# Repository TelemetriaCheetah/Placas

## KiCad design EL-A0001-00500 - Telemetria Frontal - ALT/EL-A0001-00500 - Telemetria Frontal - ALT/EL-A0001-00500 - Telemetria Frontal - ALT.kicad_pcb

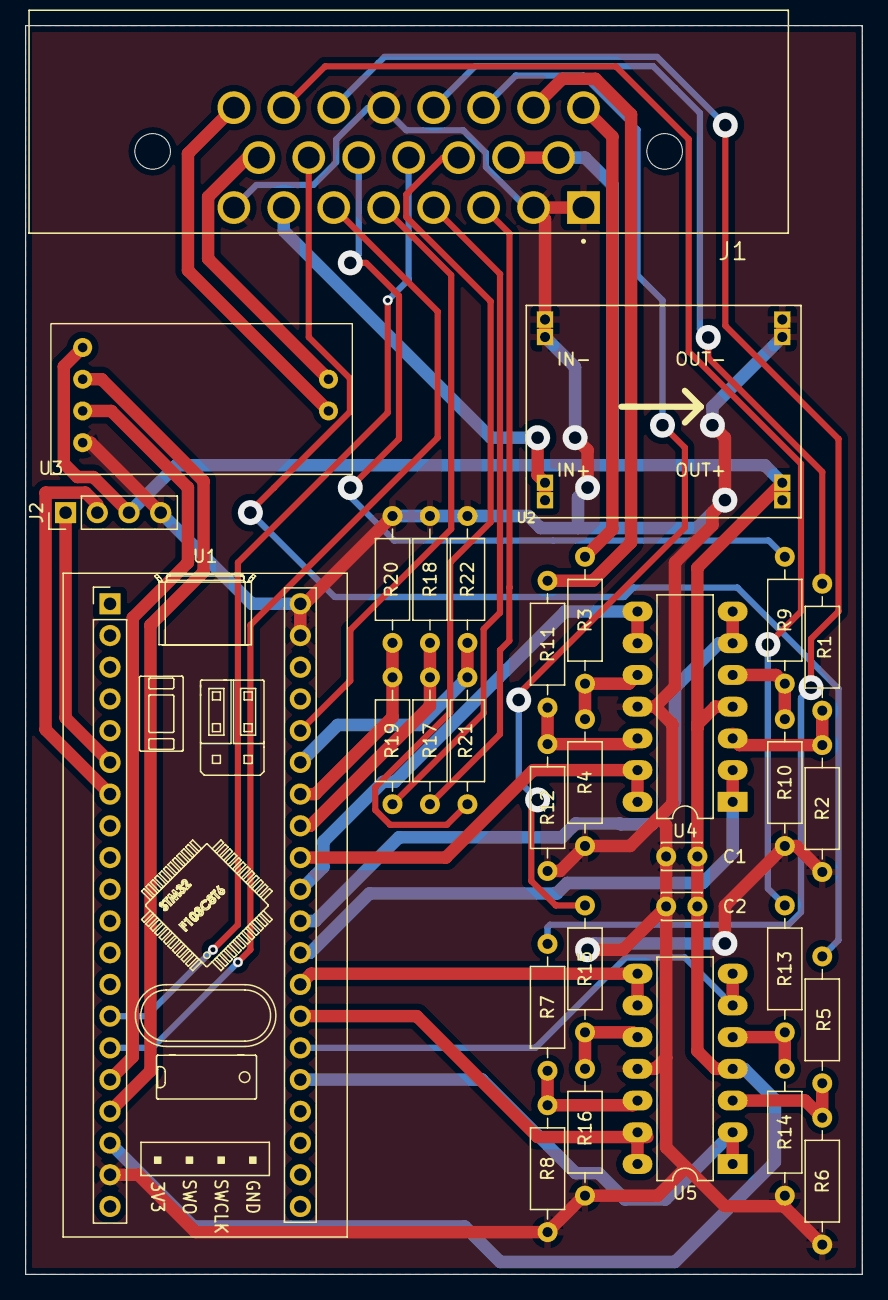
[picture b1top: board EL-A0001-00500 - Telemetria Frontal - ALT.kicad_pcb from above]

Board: 2 copper layers, 67.0 x 100.0 mm, 31 parts (0 on the bottom side), 42 nets.

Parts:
C1, C2: 100nF; C_Disc_D3.0mm_W2.0mm_P2.50mm
J1: 1-776087-1; TE_1-776087-1
J2: UART; PinHeader_1x04_P2.54mm_Vertical
R1, R2, R3, R4, R5, R6, R7, R8, R9, R10, R11, R12, R13, R14, R15, R16, R18, R20, R22: 10K; R_Axial_DIN0207_L6.3mm_D2.5mm_P10.16mm_Horizontal
R17, R19, R21: 30K; R_Axial_DIN0207_L6.3mm_D2.5mm_P10.16mm_Horizontal
U1: YAAJ_BluePill; YAAJ_BluePill_1
U2: MP1584; DC-BRICK
U3: TJA1050-Module
U4, U5: LM324; DIP-14_W7.62mm_LongPads

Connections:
+5V: C1.1, C2.1, J1.9, J1.10, J2.3, U1.18 (5V), U2.7 (VOUT+), U2.8 (VOUT+), U3.1 (VCC), U4.4 (V+), U5.4 (V+)
+12V: J1.7, U2.3 (VIN+), U2.4 (VIN+)
ADC_IN_1: J1.14, R5.1
ADC_IN_2: J1.22, R13.1
ADC_IN_3: J1.21, R7.1
ADC_OUT_1: U1.25 (PA0), U5.1, U5.2 (-)
ADC_OUT_2: U1.26 (PA1), U5.6 (-), U5.7
ADC_OUT_3: U1.27 (PA2), U5.13 (-), U5.14
BOTS_IN: J1.3, R17.1
BOTS_OUT: R17.2, R18.1, U1.33 (PB0)
CAN_H: J1.15, U3.5 (CANH)
CAN_L: J1.23, U3.6 (CANL)
CAN_RX: U1.16 (PB8), U3.3 (RX)
CAN_TX: U1.17 (PB9), U3.2 (TX)
FREIOS_IN_1: J1.13, R9.1
FREIOS_IN_2: J1.16, R3.1
FREIOS_IN_3: J1.17, R11.1
FREIOS_OUT_1: U1.30 (PA5), U4.6 (-), U4.7
FREIOS_OUT_2: U1.31 (PA6), U4.8, U4.9 (-)
FREIOS_OUT_3: U1.32 (PA7), U4.13 (-), U4.14
GND: C1.2, C2.2, J1.1, J1.2, J1.8, J1.20, J2.4, R2.2, R4.2, R6.2, R8.2, R10.2, R12.2, R14.2, R16.2, R18.2, R20.2, R22.2, U1.19 (GND), U1.39 (GND), U1.40 (GND), U2.1 (VIN-), U2.2 (VIN-), U2.5 (VOUT-), U2.6 (VOUT-), U3.4 (GND), U4.11 (V-), U5.11 (V-)
INERTIA_IN: J1.4, R19.1
INERTIA_OUT: R19.2, R20.1, U1.34 (PB1)
unnamed: J2.1, U1.6 (PA9)
unnamed: J2.2, U1.7 (PA10)
unnamed: R1.2, R2.1, U4.3 (+)
unnamed: R3.2, R4.1, U4.10 (+)
unnamed: R5.2, R6.1, U5.3 (+)
unnamed: R7.2, R8.1, U5.12 (+)
unnamed: R9.2, R10.1, U4.5 (+)
unnamed: R11.2, R12.1, U4.12 (+)
unnamed: R13.2, R14.1, U5.5 (+)
unnamed: R15.2, R16.1, U5.10 (+)
PWT_IN_1: J1.5, U1.36 (PB11)
PWT_IN_2: J1.6, U1.15 (PB7)
PWT_IN_4: J1.12, U1.14 (PB6)
SHUT_IN: J1.11, R21.1
SHUT_OUT: R21.2, R22.1, U1.35 (PB10)
TPS_IN_1: J1.18, R15.1
TPS_IN_2: J1.19, R1.1
TPS_OUT_1: U1.28 (PA3), U5.8, U5.9 (-)
TPS_OUT_2: U1.29 (PA4), U4.1, U4.2 (-)

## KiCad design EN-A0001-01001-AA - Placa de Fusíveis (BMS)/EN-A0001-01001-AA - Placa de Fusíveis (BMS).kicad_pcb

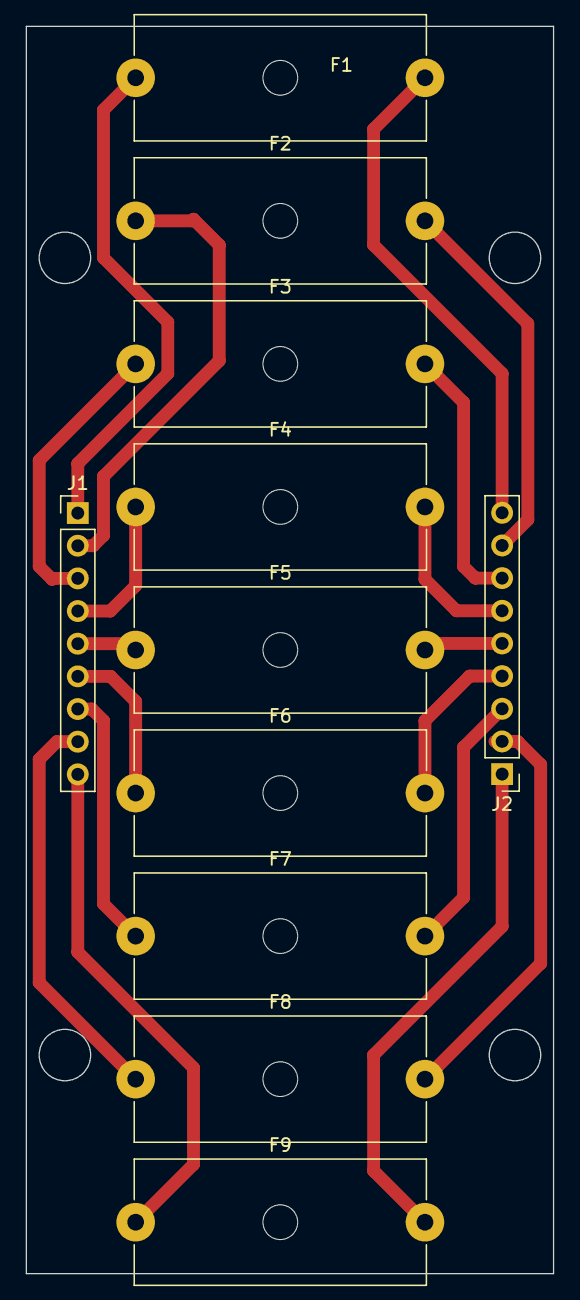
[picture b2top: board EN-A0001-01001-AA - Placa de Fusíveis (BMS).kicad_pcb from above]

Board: 2 copper layers, 41.0 x 97.0 mm, 11 parts (0 on the bottom side), 18 nets.

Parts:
F1, F2, F3, F4, F5, F6, F7, F8, F9: Fuse; Fuseholder_Cylinder-5x20mm_Schurter_0031_8201_Horizontal_Op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
J1, J2: Conn_01x09_Male; PinHeader_1x09_P2.54mm_Vertical

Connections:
unnamed: F1.1, J1.1
unnamed: F1.2, J2.9
unnamed: F2.1, J1.2
unnamed: F2.2, J2.8
unnamed: F3.1, J1.3
unnamed: F3.2, J2.7
unnamed: F4.1, J1.4
unnamed: F4.2, J2.6
unnamed: F5.1, J1.5
unnamed: F5.2, J2.5
unnamed: F6.1, J1.6
unnamed: F6.2, J2.4
unnamed: F7.1, J1.7
unnamed: F7.2, J2.3
unnamed: F8.1, J1.8
unnamed: F8.2, J2.2
unnamed: F9.1, J1.9
unnamed: F9.2, J2.1

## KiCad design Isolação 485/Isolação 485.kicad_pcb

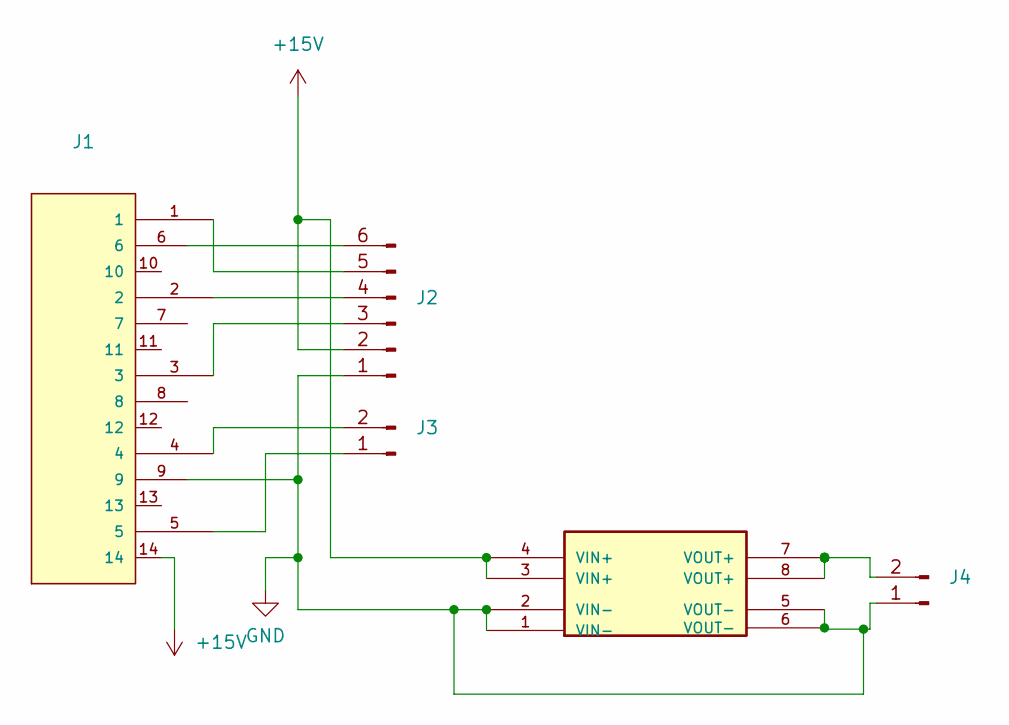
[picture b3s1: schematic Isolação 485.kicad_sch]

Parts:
J1: 776266-2
J2: Conn_01x06_Male
J3: Conn_01x02_Male
J4: (no value)
U1: MP1584

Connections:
+15V: J1.14, J2.2, U1.3 (VIN+), U1.4 (VIN+)
GND: J1.9, J2.1, J4.1, U1.1 (VIN-), U1.2 (VIN-), U1.5 (VOUT-), U1.6 (VOUT-)
unnamed: J1.2, J2.4
unnamed: J1.6, J2.6
unnamed: J1.3, J2.3
unnamed: J1.1, J2.5
unnamed: J1.5, J3.1
unnamed: J1.4, J3.2
unnamed: J4.2, U1.7 (VOUT+), U1.8 (VOUT+)

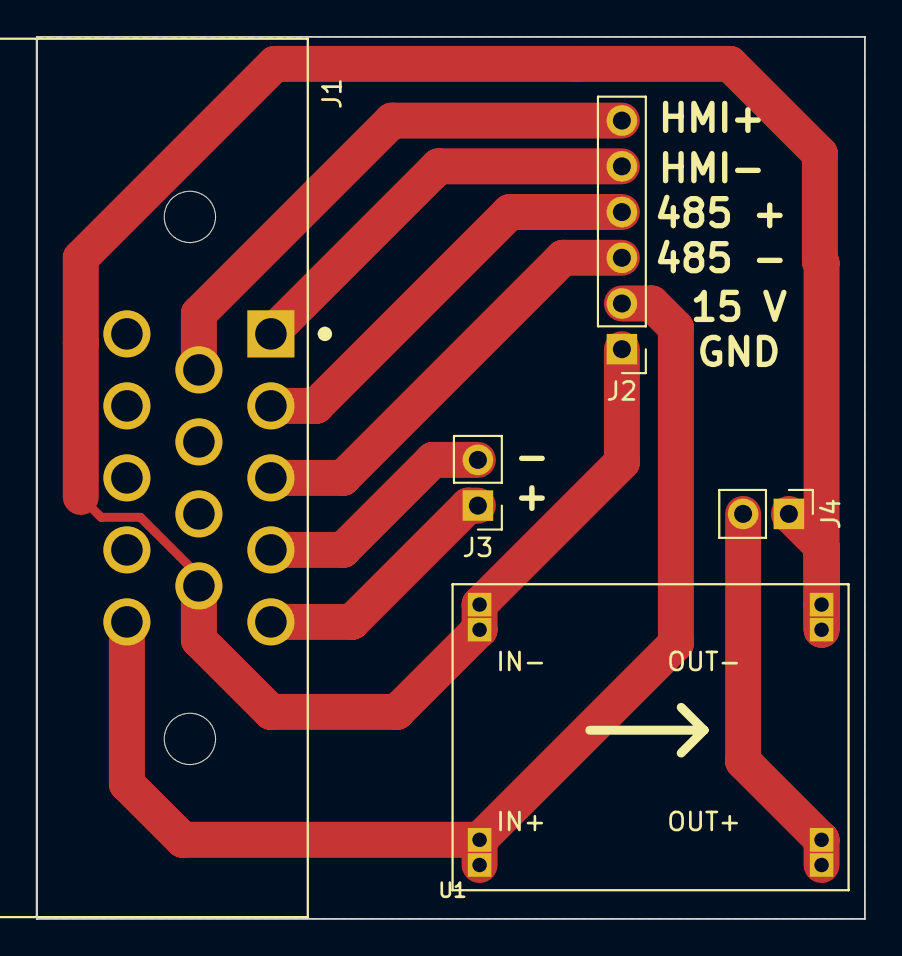
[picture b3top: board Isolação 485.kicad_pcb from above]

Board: 2 copper layers, 46.0 x 49.0 mm, 5 parts (0 on the bottom side), 9 nets.

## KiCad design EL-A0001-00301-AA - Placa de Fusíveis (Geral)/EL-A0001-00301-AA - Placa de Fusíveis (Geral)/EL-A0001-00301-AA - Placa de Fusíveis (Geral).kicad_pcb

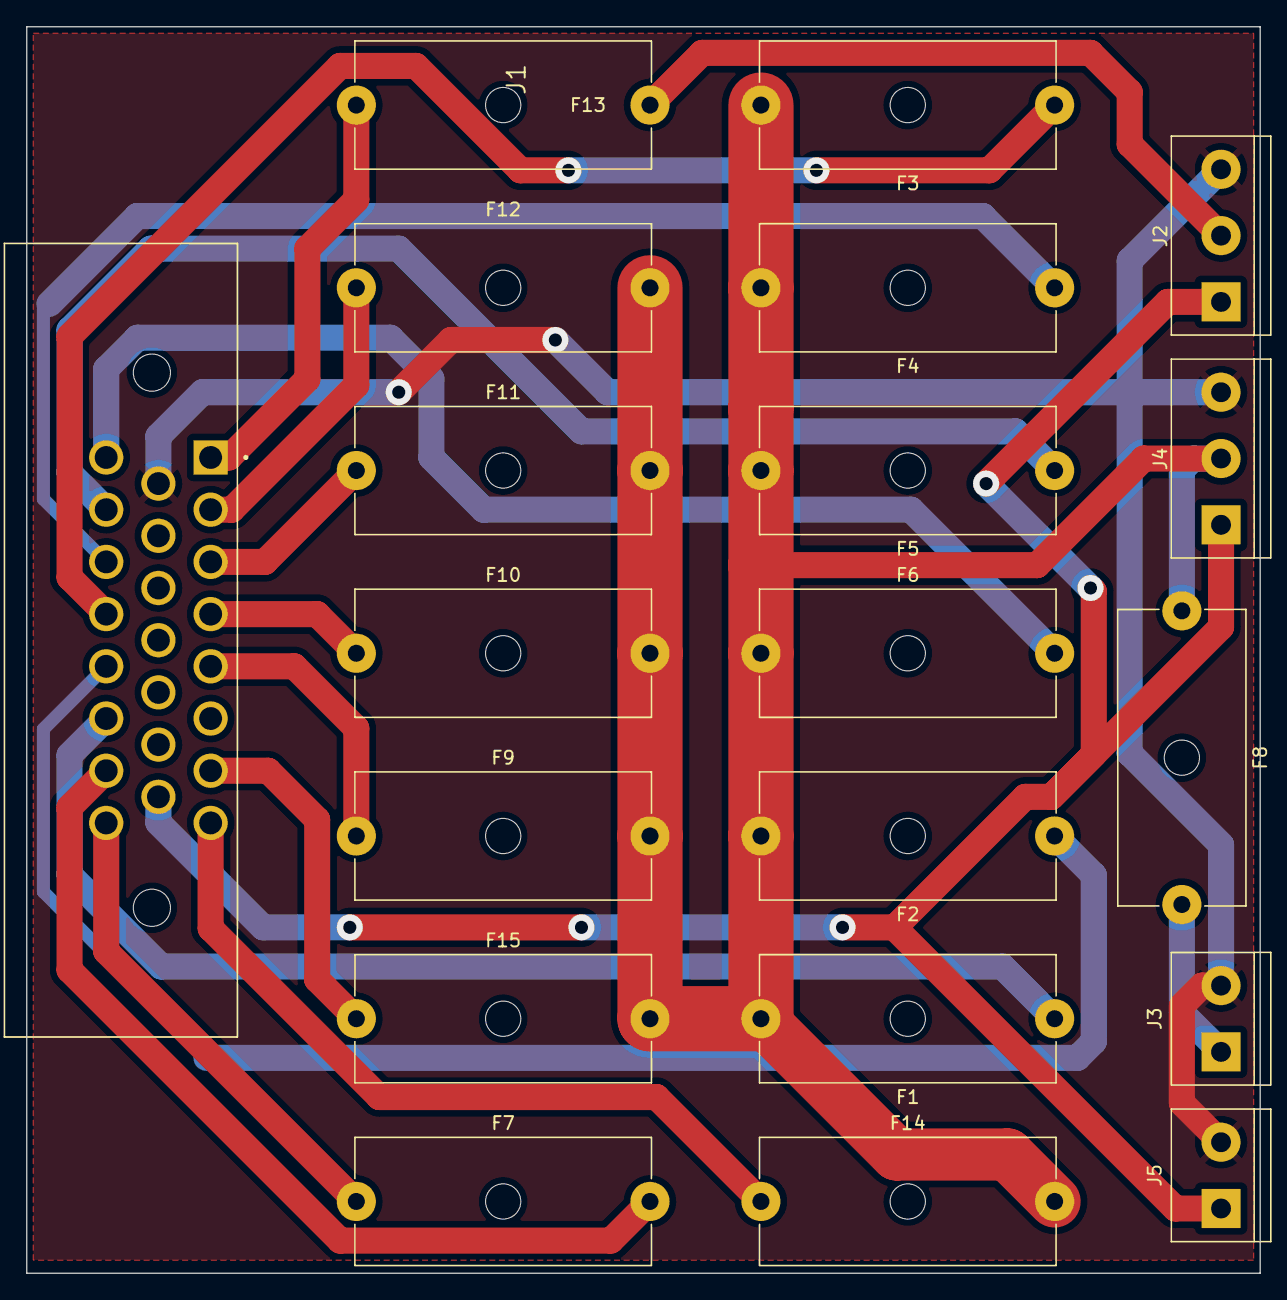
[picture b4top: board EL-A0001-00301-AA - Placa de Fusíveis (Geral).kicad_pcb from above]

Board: 2 copper layers, 94.5 x 95.5 mm, 20 parts (0 on the bottom side), 20 nets.

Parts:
F1, F2, F3, F4, F5, F6, F9, F10, F11, F12, F14, F15: Fuse; Fuseholder_Cylinder-5x20mm_Schurter_0031_8201_Horizontal_Op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
F7: GLV_FUSE; Fuseholder_Cylinder-5x20mm_Schurter_0031_8201_Horizontal_Op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
F8: SPLIT_FUSE; Fuseholder_Cylinder-5x20mm_Schurter_0031_8201_Horizontal_Op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
F13: SHUT_FUSE; Fuseholder_Cylinder-5x20mm_Schurter_0031_8201_Horizontal_Op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
J1: 1-776087-1; TE_1-776087-1
J2: BUCK_SHUT; TerminalBlock_bornier-3_P5.08mm
J3: SPLIT_POWER; TerminalBlock_bornier-2_P5.08mm
J4: DC_CONVERTER; TerminalBlock_bornier-3_P5.08mm
J5: VBAT; TerminalBlock_bornier-2_P5.08mm

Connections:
12V: F1.2, F2.2, F3.2, F4.2, F5.2, F6.2, F8.1, F9.2, F10.2, F11.2, F12.2, F14.2, F15.2, J4.2
GND: J1.9, J2.3, J3.2, J4.3, J5.2
unnamed: F1.1, J1.21
unnamed: F2.1, J1.20
unnamed: F3.1, J1.19
unnamed: F4.1, J1.18
unnamed: F5.1, J1.17
unnamed: F6.1, J1.16
unnamed: F7.1, J1.23
unnamed: F8.2, J3.1
unnamed: F9.1, J1.5
unnamed: F10.1, J1.4
unnamed: F11.1, J1.3
unnamed: F12.1, J1.2
unnamed: F14.1, J1.8
unnamed: F15.1, J1.7
unnamed: F13.1, J1.1
unnamed: F7.2, J1.22
unnamed: F13.2, J2.2
VBAT: J1.15, J2.1, J4.1, J5.1

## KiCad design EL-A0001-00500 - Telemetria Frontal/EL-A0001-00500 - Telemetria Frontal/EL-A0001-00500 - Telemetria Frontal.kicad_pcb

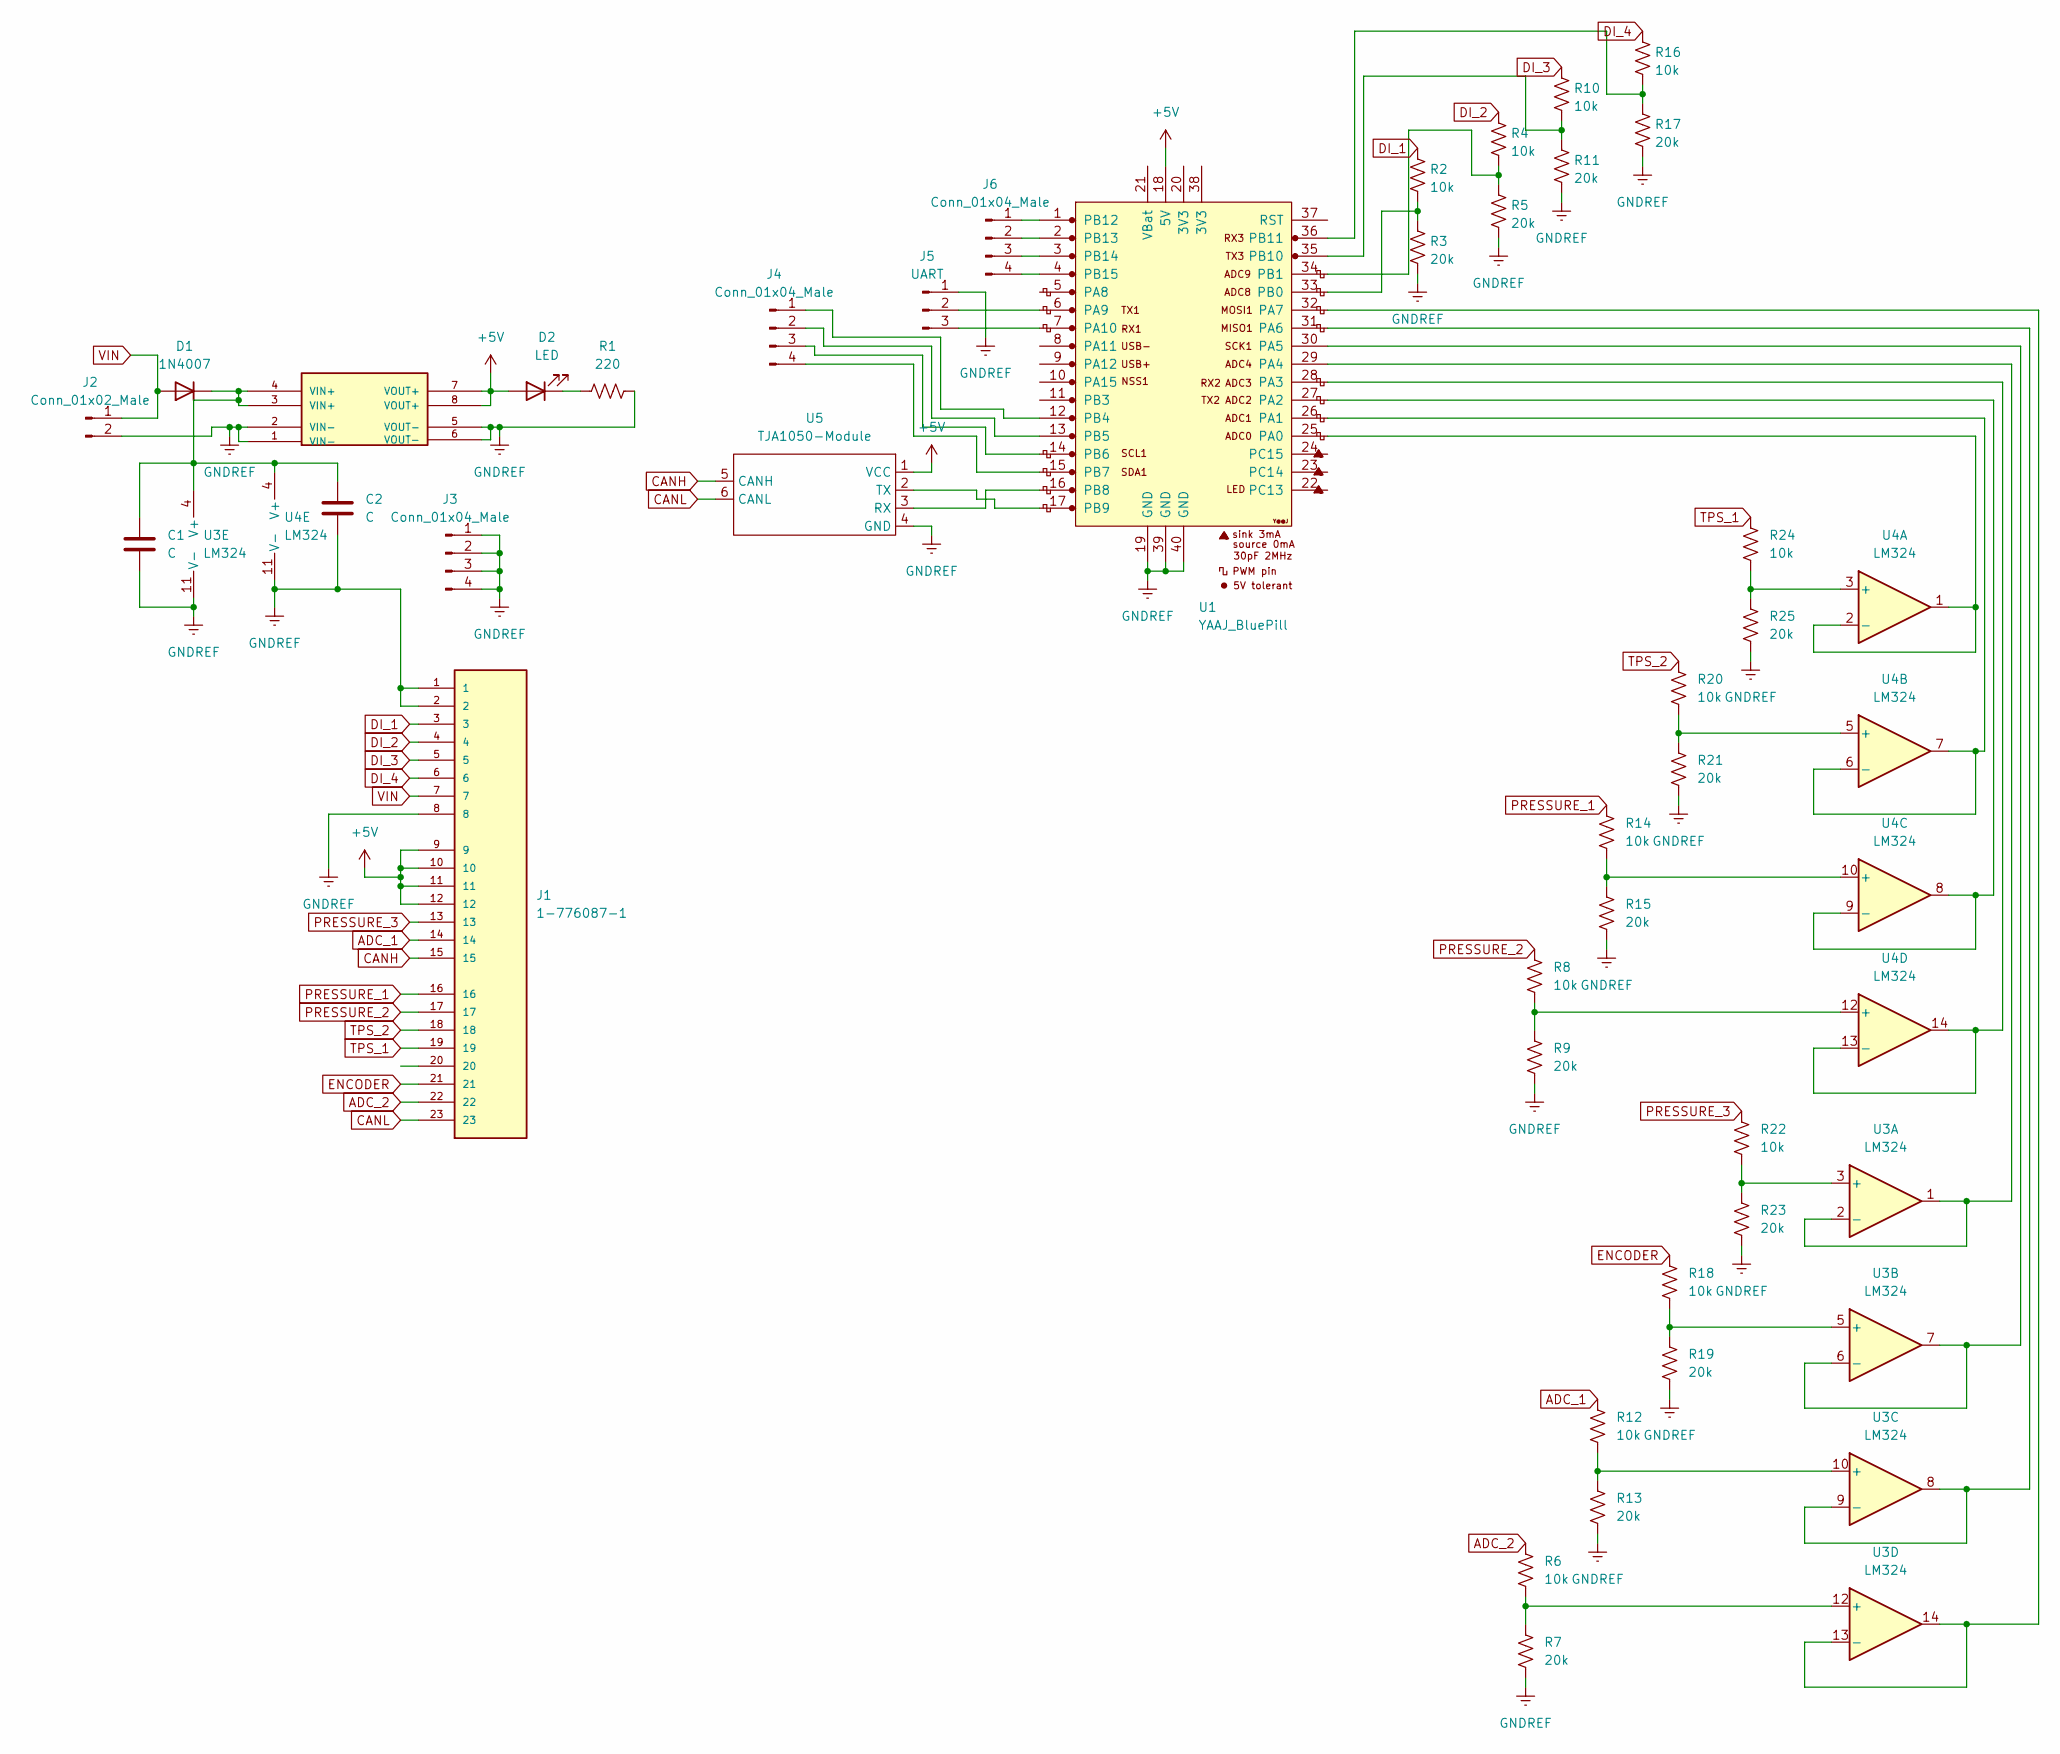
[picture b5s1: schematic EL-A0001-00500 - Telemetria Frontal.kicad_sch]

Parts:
C1, C2: C; C_0805_2012Metric
D1: 1N4007; D_DO-41_SOD81_P10.16mm_Horizontal
D2: LED; LED_D5.0mm
J1: 1-776087-1; TE_1-776087-1
J2: Conn_01x02_Male; PinHeader_1x02_P2.54mm_Vertical
J3, J4, J6: Conn_01x04_Male; PinHeader_1x04_P2.54mm_Vertical
J5: UART; PinHeader_1x03_P2.54mm_Vertical
R1: 220; R_0805_2012Metric
R2, R4, R10, R16: 10k; R_Axial_DIN0207_L6.3mm_D2.5mm_P10.16mm_Horizontal
R3, R5, R11, R17: 20k; R_Axial_DIN0207_L6.3mm_D2.5mm_P10.16mm_Horizontal
R6, R8, R12, R14, R18, R20, R22, R24: 10k; R_0805_2012Metric
R7, R9, R13, R15, R19, R21, R23, R25: 20k; R_0805_2012Metric
U1: YAAJ_BluePill; YAAJ_BluePill_1
U2: MP1584; DC-BRICK
U3, U4: LM324; DIP-14_W7.62mm_LongPads
U5: TJA1050-Module

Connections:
+5V: D2.2 (A), J1.9, J1.10, J1.11, J1.12, U1.18 (5V), U2.7 (VOUT+), U2.8 (VOUT+), U5.1 (VCC)
ADC_1: J1.14, R12.2
ADC_2: J1.22, R6.2
CANH: J1.15, U5.5 (CANH)
CANL: J1.23, U5.6 (CANL)
DI_1: J1.3, R2.2
DI_2: J1.4, R4.2
DI_3: J1.5, R10.2
DI_4: J1.6, R16.2
ENCODER: J1.21, R18.2
GNDREF: C1.2, C2.2, J1.1, J1.2, J1.8, J2.2, J3.1, J3.2, J3.3, J3.4, J5.1, R1.2, R3.1, R5.1, R7.1, R9.1, R11.1, R13.1, R15.1, R17.1, R19.1, R21.1, R23.1, R25.1, U1.19 (GND), U1.39 (GND), U1.40 (GND), U2.1 (VIN-), U2.2 (VIN-), U2.5 (VOUT-), U2.6 (VOUT-), U3.11 (V-), U4.11 (V-), U5.4 (GND)
unnamed: C1.1, C2.1, D1.1 (K), U2.3 (VIN+), U2.4 (VIN+), U3.4 (V+), U4.4 (V+)
unnamed: D2.1 (K), R1.1
unnamed: J4.1, U1.12 (PB4)
unnamed: J4.2, U1.13 (PB5)
unnamed: J4.3, U1.14 (PB6)
unnamed: J4.4, U1.15 (PB7)
unnamed: J5.2, U1.6 (PA9)
unnamed: J5.3, U1.7 (PA10)
unnamed: J6.1, U1.1 (PB12)
unnamed: J6.2, U1.2 (PB13)
unnamed: J6.3, U1.3 (PB14)
unnamed: J6.4, U1.4 (PB15)
unnamed: R2.1, R3.2, U1.33 (PB0)
unnamed: R4.1, R5.2, U1.34 (PB1)
unnamed: R6.1, R7.2, U3.12 (+)
unnamed: R8.1, R9.2, U4.12 (+)
unnamed: R10.1, R11.2, U1.35 (PB10)
unnamed: R12.1, R13.2, U3.10 (+)
unnamed: R14.1, R15.2, U4.10 (+)
unnamed: R16.1, R17.2, U1.36 (PB11)
unnamed: R18.1, R19.2, U3.5 (+)
unnamed: R20.1, R21.2, U4.5 (+)
unnamed: R22.1, R23.2, U3.3 (+)
unnamed: R24.1, R25.2, U4.3 (+)
unnamed: U1.16 (PB8), U5.3 (RX)
unnamed: U1.17 (PB9), U5.2 (TX)
unnamed: U1.25 (PA0), U4.1, U4.2 (-)
unnamed: U1.26 (PA1), U4.6 (-), U4.7
unnamed: U1.27 (PA2), U4.8, U4.9 (-)
unnamed: U1.28 (PA3), U4.13 (-), U4.14
unnamed: U1.29 (PA4), U3.1, U3.2 (-)
unnamed: U1.30 (PA5), U3.6 (-), U3.7
unnamed: U1.31 (PA6), U3.8, U3.9 (-)
unnamed: U1.32 (PA7), U3.13 (-), U3.14
PRESSURE_1: J1.16, R14.2
PRESSURE_2: J1.17, R8.2
PRESSURE_3: J1.13, R22.2
TPS_1: J1.19, R24.2
TPS_2: J1.18, R20.2
VIN: D1.2 (A), J1.7, J2.1

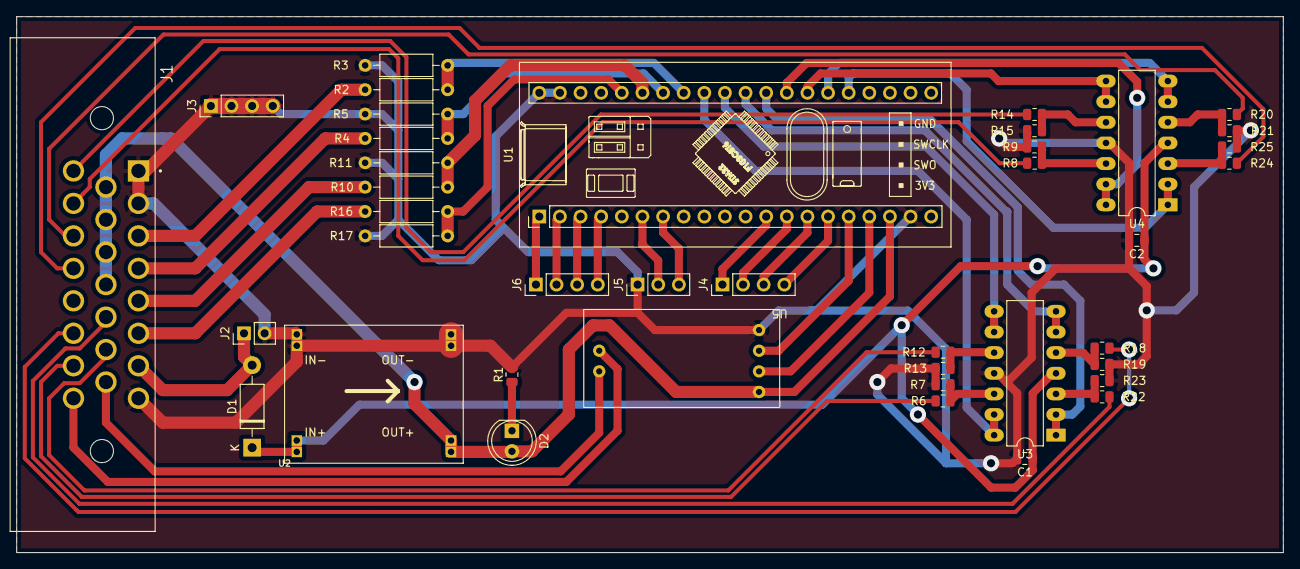
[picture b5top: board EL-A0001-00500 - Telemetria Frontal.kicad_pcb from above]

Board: 2 copper layers, 156.0 x 66.0 mm, 40 parts (0 on the bottom side), 51 nets.

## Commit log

2022-03-12 ADD: Commit Inicial
2022-03-12 ADD: Telemetria Frontal
2022-03-12 ADD: submodules
2022-03-13 ADD: placa de fusiveis
2022-03-13 MOD: placa de fusiveis
2022-03-13 MOD: delete backup
2022-03-13 ADD:Fabricação
2022-03-13 Telemetria frontal
2022-03-14 ADD: fusiveis BMS
2022-03-14 ADD: fusiveis
2022-03-14 ADD: placas
2022-03-17 FIX: panel border
2022-04-19 ADD: Tele traseira ALT
2022-04-25 ADD: tele frontal alt
2022-04-28 MOD: placa de fusiveis nova
2022-04-28 MOD: placa de telemetria frontal ALT
